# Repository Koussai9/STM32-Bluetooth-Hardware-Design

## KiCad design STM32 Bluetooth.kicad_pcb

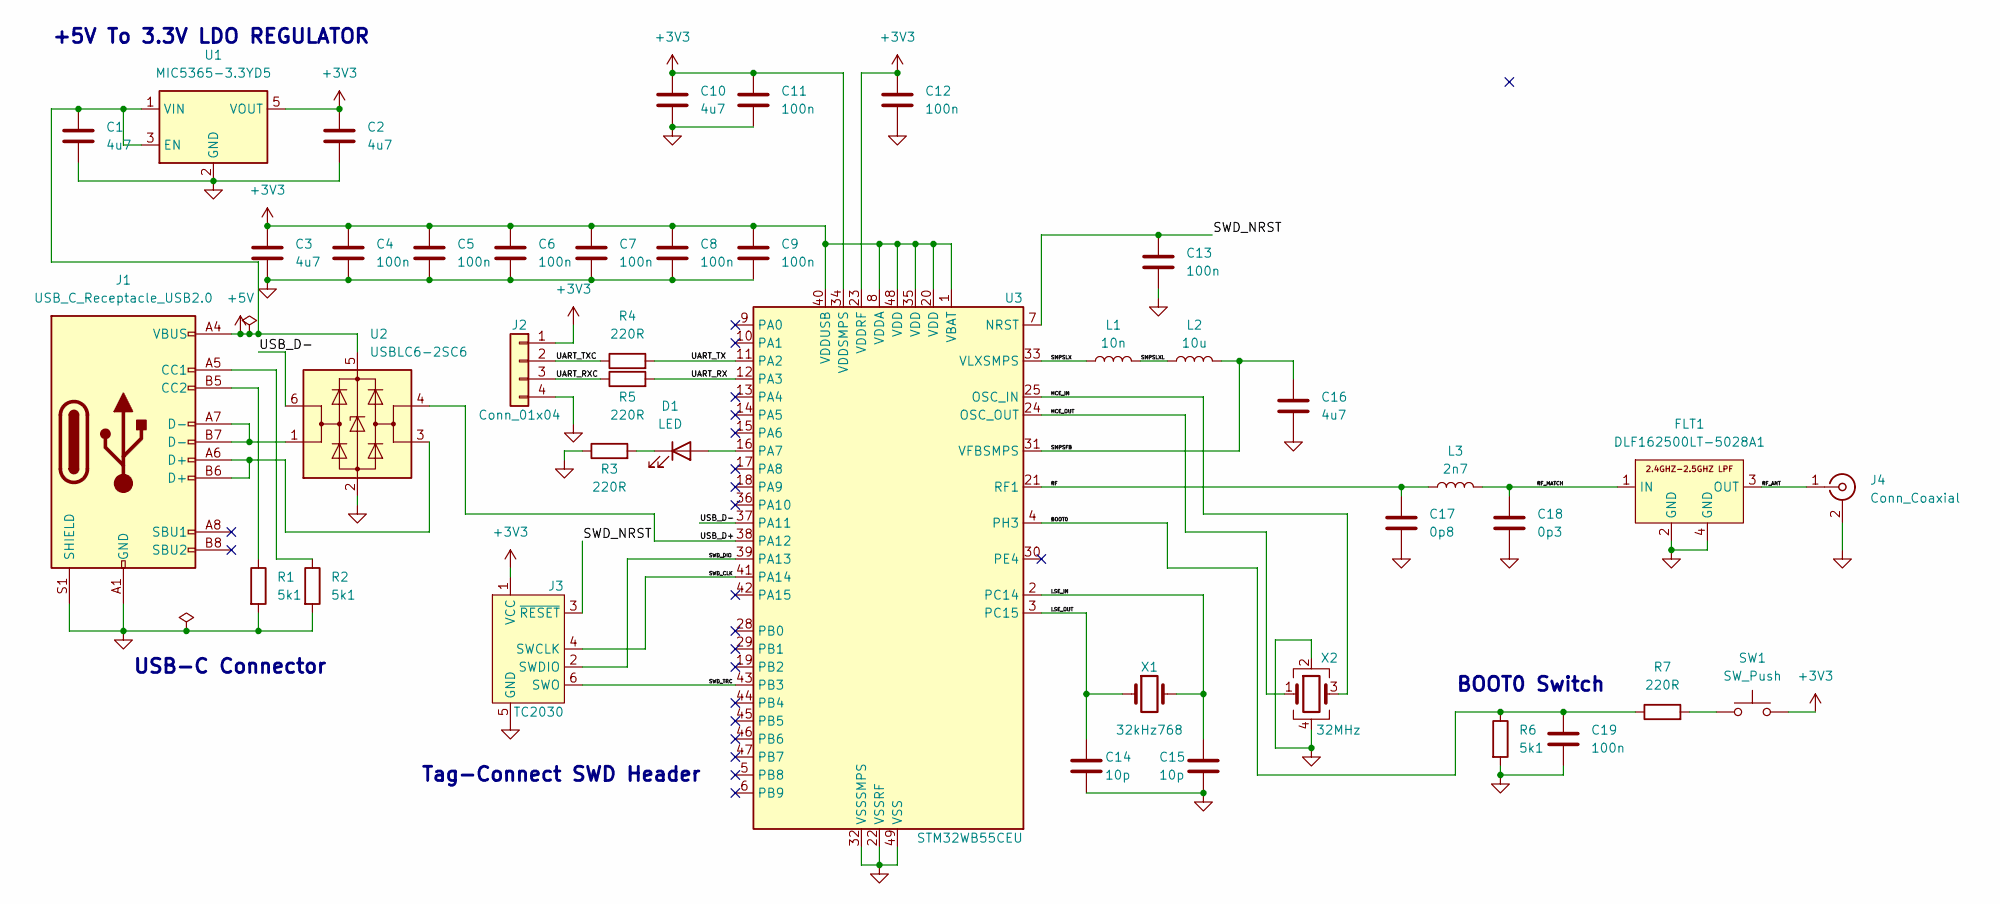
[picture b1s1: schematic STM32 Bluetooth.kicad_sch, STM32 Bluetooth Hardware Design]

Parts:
C1, C2, C3, C10, C16: 4u7; C_0603_1608Metric
C4, C5, C6, C7, C8, C9, C11, C12, C13, C19: 100n; C_0402_1005Metric
C14, C15: 10p; C_0402_1005Metric
C17: 0p8; C_0402_1005Metric
C18: 0p3; C_0402_1005Metric
D1: LED; LED_0402_1005Metric
FLT1: DLF162500LT-5028A1
J1: USB_C_Receptacle_USB2.0; USB_C_Receptacle_GCT_USB4105-xx-A_16P_TopMnt_Horizontal
J2: Conn_01x04; Molex_PicoBlade_53048-0410_1x04_P1.25mm_Horizontal
J3: TC2030; Tag-Connect_TC2030-IDC-FP_2x03_P1.27mm_Vertical
J4: Conn_Coaxial; U.FL_Hirose_U.FL-R-SMT-1_Vertical
L1: 10n; L_0402_1005Metric
L2: 10u; L_0805_2012Metric
L3: 2n7; L_0402_1005Metric
R1, R2, R6: 5k1; R_0402_1005Metric
R3, R4, R5, R7: 220R; R_0402_1005Metric
SW1: SW_Push; SW_SPST_CK_RS282G05A3
U1: MIC5365-3.3YD5; SOT-23-5
U2: USBLC6-2SC6; SOT-23-6
U3: STM32WB55CEU; QFN-48-1EP_7x7mm_P0.5mm_EP5.6x5.6mm
X1: 32kHz768; Crystal_SMD_2012-2Pin_2.0x1.2mm
X2: 32MHz; Crystal_SMD_2016-4Pin_2.0x1.6mm

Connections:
+3V3: C2.1, C3.1, C4.1, C5.1, C6.1, C7.1, C8.1, C9.1, C10.1, C11.1, C12.1, J2.1, J3.1 (VCC), SW1.2, U1.5 (VOUT), U3.1 (VBAT), U3.8 (VDDA), U3.20 (VDD), U3.23 (VDDRF), U3.34 (VDDSMPS), U3.35 (VDD), U3.40 (VDDUSB), U3.48 (VDD)
+5V: C1.1, J1.A4 (VBUS), J1.A9 (VBUS), J1.B4 (VBUS), J1.B9 (VBUS), U1.1 (VIN), U1.3 (EN), U2.5 (VBUS)
/BOOT0: C19.1, R6.1, R7.1, U3.4 (PH3)
/HCE_IN: U3.25 (OSC_IN), X2.3
/HCE_OUT: U3.24 (OSC_OUT), X2.1
/LSE_IN: C15.1, U3.2 (PC14), X1.2
/LSE_OUT: C14.1, U3.3 (PC15), X1.1
/RF: C17.1, L3.1, U3.21 (RF1)
/RF_ANT: FLT1.3 (OUT), J4.1 (In)
/RF_MATCH: C18.1, FLT1.1 (IN), L3.2
/SMPSFB: C16.1, L2.2, U3.31 (VFBSMPS)
/SMPSLX: L1.1, U3.33 (VLXSMPS)
/SMPSLXL: L1.2, L2.1
/SWD_CLK: J3.4 (SWCLK), U3.41 (PA14)
/SWD_DIO: J3.2 (SWDIO), U3.39 (PA13)
/SWD_NRST: C13.1, J3.3 (~RESET), U3.7 (NRST)
/SWD_TRC: J3.6 (SWO), U3.43 (PB3)
/UART_RX: R5.2, U3.12 (PA3)
/UART_RXC: J2.3, R5.1
/UART_TX: R4.2, U3.11 (PA2)
/UART_TXC: J2.2, R4.1
/USB_D+: U2.4 (I/O2), U3.38 (PA12)
/USB_D-: U2.6 (I/O1), U3.37 (PA11)
GND: C1.2, C2.2, C3.2, C4.2, C5.2, C6.2, C7.2, C8.2, C9.2, C10.2, C11.2, C12.2, C13.2, C14.2, C15.2, C16.2, C17.2, C18.2, C19.2, FLT1.2 (GND), FLT1.4 (GND), J1.A1 (GND), J1.A12 (GND), J1.B1 (GND), J1.B12 (GND), J1.S1 (SHIELD), J2.4, J3.5 (GND), J4.2 (Ext), R1.2, R2.2, R3.1, R6.2, U1.2 (GND), U2.2 (GND), U3.22 (VSSRF), U3.32 (VSSSMPS), U3.49 (VSS), X2.2, X2.4
unnamed: D1.2 (A), U3.16 (PA7)
unnamed: D1.1 (K), R3.2
unnamed: J1.A5 (CC1), R2.1
unnamed: J1.B5 (CC2), R1.1
unnamed: J1.A6 (D+), J1.B6 (D+), U2.3 (I/O2)
unnamed: J1.A7 (D-), J1.B7 (D-), U2.1 (I/O1)
unnamed: R7.2, SW1.1

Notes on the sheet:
Tag-Connect SWD Header
BOOT0 Switch
+5V To 3.3V LDO REGULATOR
USB-C Connector

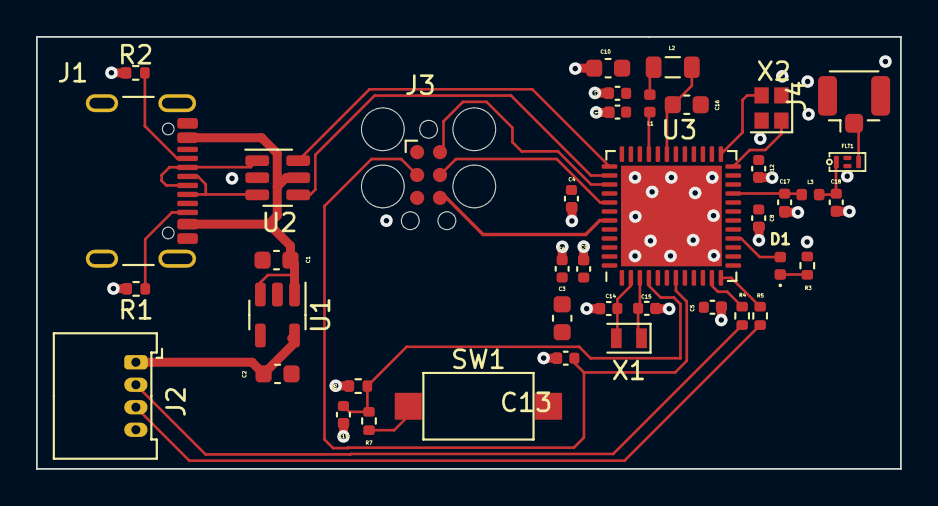
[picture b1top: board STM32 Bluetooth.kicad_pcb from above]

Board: 4 copper layers, 48.0 x 24.0 mm, 41 parts (0 on the bottom side), 31 nets.
